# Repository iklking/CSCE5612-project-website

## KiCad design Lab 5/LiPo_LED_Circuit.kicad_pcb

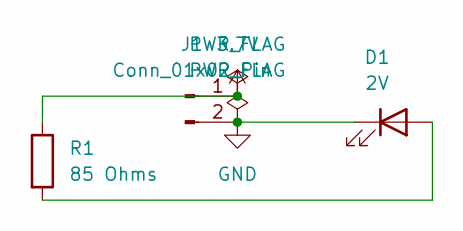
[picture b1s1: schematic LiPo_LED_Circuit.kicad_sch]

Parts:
D1: 2V; LED_D3.0mm
J1: Conn_01x02_Pin; JST_PH_S2B-PH-K_1x02_P2.00mm_Horizontal
R1: 85 Ohms; R_Axial_DIN0207_L6.3mm_D2.5mm_P2.54mm_Vertical

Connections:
3.7V: J1.1, R1.1
GND: D1.1 (K), J1.2
unnamed: D1.2 (A), R1.2

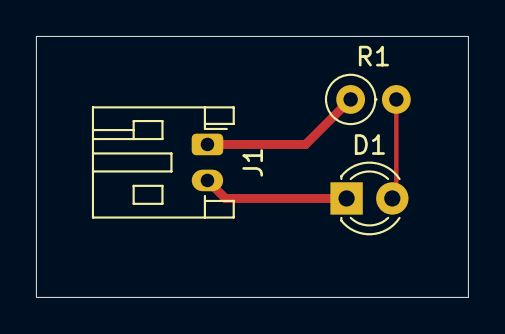
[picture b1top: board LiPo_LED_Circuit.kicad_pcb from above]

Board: 2 copper layers, 24.0 x 14.5 mm, 3 parts (0 on the bottom side), 3 nets.

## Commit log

2025-01-15 add photo
2025-01-15 Update index.html to add image
2025-01-15 Update index.html to add video
2025-01-30 adding some style elements
2025-02-05 Deleted previous updates
2025-02-05 Added Week 1 folder
2025-02-05 Rename Accelorameter.png to Week 1/Accelerometer.png
2025-02-05 Rename Blink.mp4 to Week 1/Blink.mp4
2025-02-05 Rename Bluetooth.png to Week 1/Bluetooth.png
2025-02-05 Rename BluetoothPhone.png to Week 1/BluetoothPhone.png
2025-02-05 Rename Buzzer.mp4 to Lab 2/Buzzer.mp4
2025-02-05 Rename Accelerometer.png to Accelerometer.png
2025-02-05 Rename Bluetooth.png to Bluetooth.png
2025-02-05 Rename BluetoothPhone.png to BluetoothPhone.png
2025-02-05 Rename LEDOff.jpeg to Lab 2/LEDOff.jpeg
2025-02-05 Rename LEDOn.jpeg to Lab 2/LEDOn.jpeg
2025-02-05 Rename MicroSD.mp4 to Lab 2/MicroSD.mp4
2025-02-05 Rename MicroSD.png to Lab 2/MicroSD.png
2025-02-05 Rename Microphone.mp4 to Lab 2/Microphone.mp4
2025-02-05 Rename Microphone.png to Lab 2/Microphone.png
2025-02-05 Rename OLED.jpeg to Lab 2/OLED.jpeg
2025-02-05 Rename OLED.mp4 to Lab 2/OLED.mp4
2025-02-05 Rename Real-Time.mp4 to Lab 2/Real-Time.mp4
2025-02-05 Rename Real-Time.png to Lab 2/Real-Time.png
2025-02-05 Rename assembly.jpeg to Lab 1/assembly.jpeg
2025-02-05 Added files for Lab 3
2025-02-05 Rename Lab3.ino to Lab 3/Lab3.ino
2025-02-05 Fixing Links
2025-02-05 Added Week 3 template
2025-02-05 Trying something
2025-02-05 Added link to code
2025-02-05 Added videos and pictures for Lab 3
2025-02-06 Added diagram and equations
2025-02-12 added pictures for lab 4
2025-02-12 Rename pumch.png to Lab 4/punch.png
2025-02-12 Rename loss.png to Lab 4/loss.png
2025-02-12 Rename flex.png to Lab 4/flex.png
2025-02-12 Added lab 4
2025-02-21 added gerber files
2025-02-21 Rename Gerber files.zip to Lab 5/Gerber files.zip
2025-02-27 added lab 6
2025-02-27 added results
2025-04-24 Updating website for labs
2025-04-24 Rename esp32_camera.ino to Lab 7/esp32_camera.ino
2025-04-24 Rename Lab7-1.ino to Lab 7/Lab7-1.ino
2025-04-25 Rename Lab_8.ino to Lab 8/Lab_8.ino
2025-04-25 Rename RTOS.ino to RTOS_Pt1.ino
2025-04-25 Rename Lab 10/take_photos_wifi.ino to Lab 10/Part 7/take_photos_wifi.ino
2025-04-25 Rename Lab 10/camera_index.h to Lab 10/Part 7/camera_index.h
2025-04-25 Rename Lab 10/camera_pins.h to Lab 10/Part 7/camera_pins.h
2025-04-25 Rename Milestone 4.pdf to Project/Milestone 4.pdf
